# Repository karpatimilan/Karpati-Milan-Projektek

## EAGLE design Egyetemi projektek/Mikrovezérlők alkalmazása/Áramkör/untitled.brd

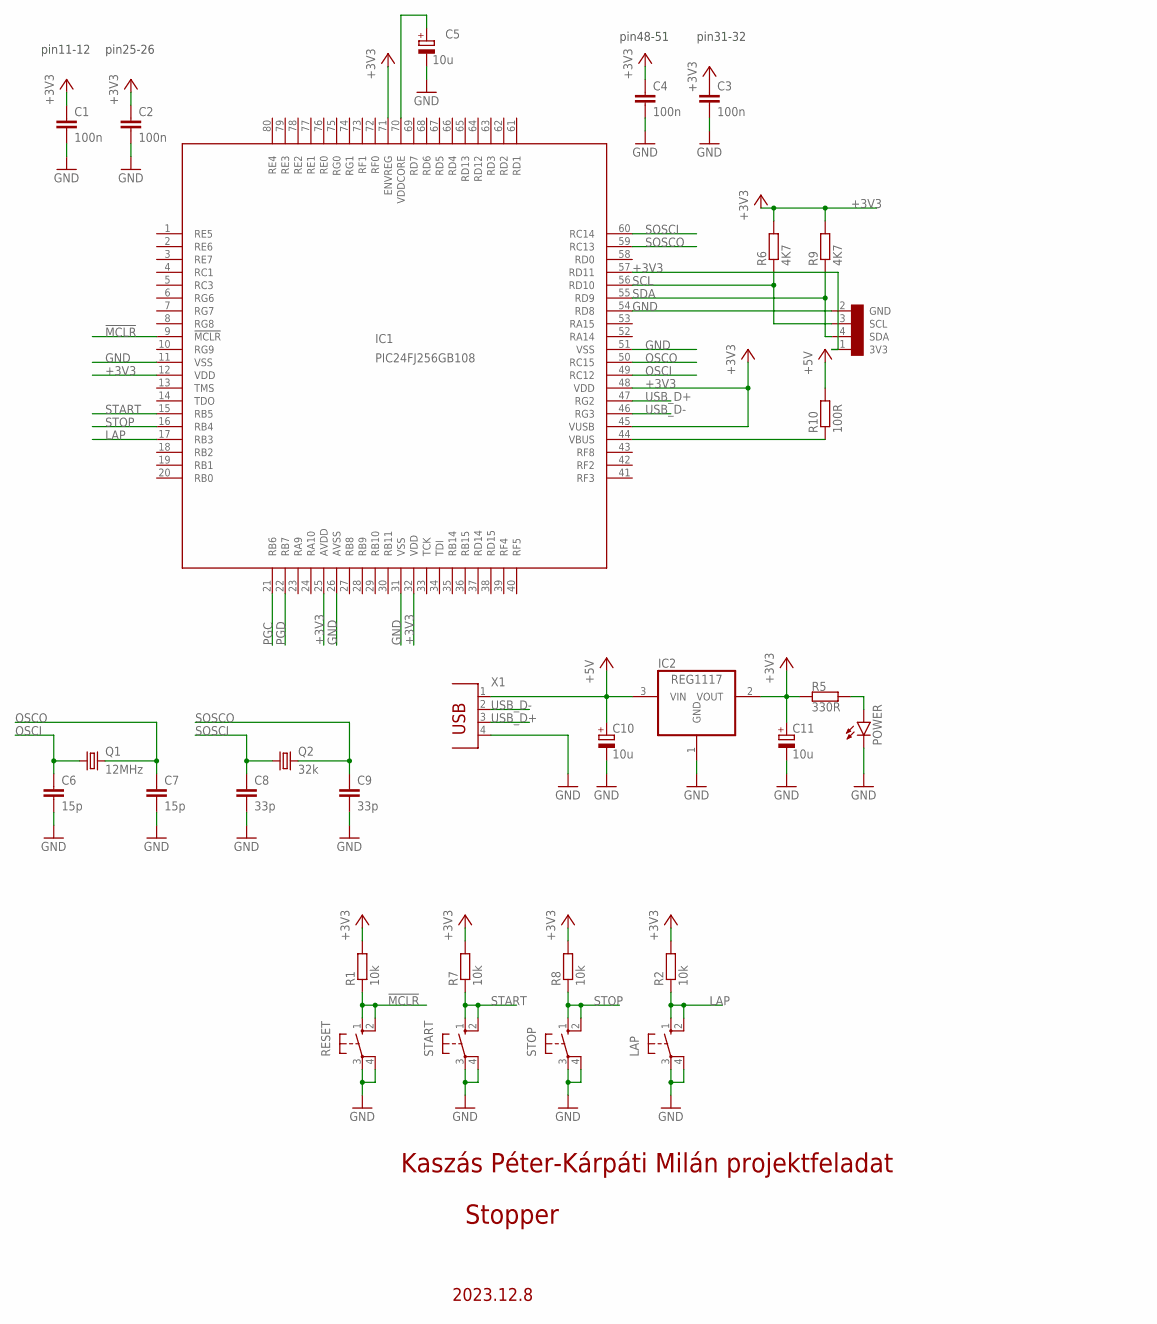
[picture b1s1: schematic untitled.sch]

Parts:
C1, C2, C3, C4: 100n; C1206
C5, C10, C11: 10u; SMC_D
C6, C7: 15p; C1206
C8, C9: 33p; C1206
CON1: ICSPI2CTUSKE; HDRV4W64P254_1X4_1016X508X838B
IC1: PIC24FJ256GB108; TQFP80-12X12
IC2: REG1117; SOT223
LAP: 10-XX; B3F-10XX
POWER: LED5MM
Q1: 12MHz; HC49U70
Q2: 32k; TC26H
R1, R2, R7, R8: 10k; R1206
R5: 330R; R1206
R6, R9: 4K7; R1206
R10: 100R; R1206
RESET: 10-XX; B3F-10XX
START: 10-XX; B3F-10XX
STOP: 10-XX; B3F-10XX
X1: PN61729

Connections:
!MCLR: IC1.9 (!MCLR), R1.1, RESET.1 (S), RESET.2 (S1)
+3V3: C1.1, C2.1, C3.1, C4.1, C11.+, CON1.1 (3V3), IC1.12 (VDD), IC1.25 (AVDD), IC1.32 (VDD), IC1.45 (VUSB), IC1.48 (VDD), IC1.57 (RD11), IC1.71 (ENVREG), IC2.2 (VOUT), R1.2, R2.2, R5.2, R6.2, R7.2, R8.2, R9.2
+5V: C10.+, IC2.3 (VIN), R10.2, X1.1
GND: C1.2, C2.2, C3.2, C4.2, C5.-, C6.2, C7.2, C8.2, C9.2, C10.-, C11.-, CON1.2 (GND), IC1.11 (VSS), IC1.26 (AVSS), IC1.31 (VSS), IC1.51 (VSS), IC1.54 (RD8), IC2.1 (GND), LAP.3, LAP.4 (P1), POWER.K (C), RESET.3, RESET.4 (P1), START.3, START.4 (P1), STOP.3, STOP.4 (P1), X1.4
LAP: IC1.17 (RB3), LAP.1 (S), LAP.2 (S1), R2.1
unnamed: C5.+, IC1.70 (VDDCORE)
unnamed: POWER.A, R5.1
unnamed: IC1.44 (VBUS), R10.1
OSCI: C6.1, IC1.49 (RC12), Q1.1
OSCO: C7.1, IC1.50 (RC15), Q1.2
PGC: IC1.21 (RB6)
PGD: IC1.22 (RB7)
SCL: CON1.3 (SCL), IC1.56 (RD10), R6.1
SDA: CON1.4 (SDA), IC1.55 (RD9), R9.1
SOSCI: C8.1, IC1.60 (RC14), Q2.1
SOSCO: C9.1, IC1.59 (RC13), Q2.2
START: IC1.15 (RB5), R7.1, START.1 (S), START.2 (S1)
STOP: IC1.16 (RB4), R8.1, STOP.1 (S), STOP.2 (S1)
USB_D+: IC1.47 (RG2), X1.3
USB_D-: IC1.46 (RG3), X1.2

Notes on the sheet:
pin11-12
pin25-26
pin31-32
pin48-51
Stopper
2023.12.8
Kaszás Péter-Kárpáti Milán projektfeladat

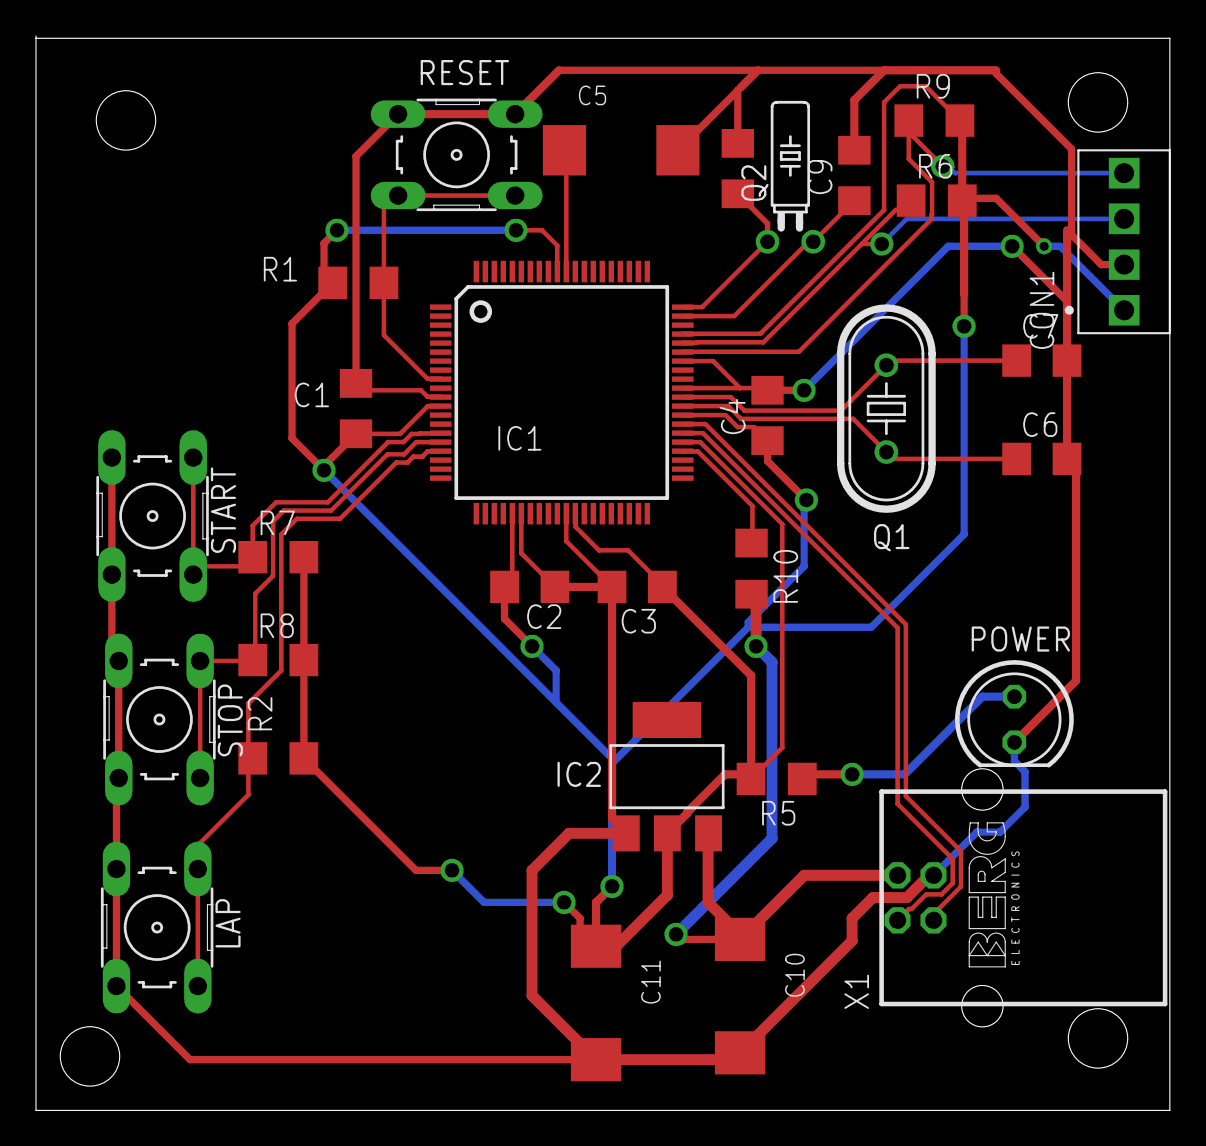
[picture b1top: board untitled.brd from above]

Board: 2 copper layers, 63.0 x 59.6 mm, 30 parts (0 on the bottom side), 18 nets.

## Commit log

2024-12-08 szakdolgozat
